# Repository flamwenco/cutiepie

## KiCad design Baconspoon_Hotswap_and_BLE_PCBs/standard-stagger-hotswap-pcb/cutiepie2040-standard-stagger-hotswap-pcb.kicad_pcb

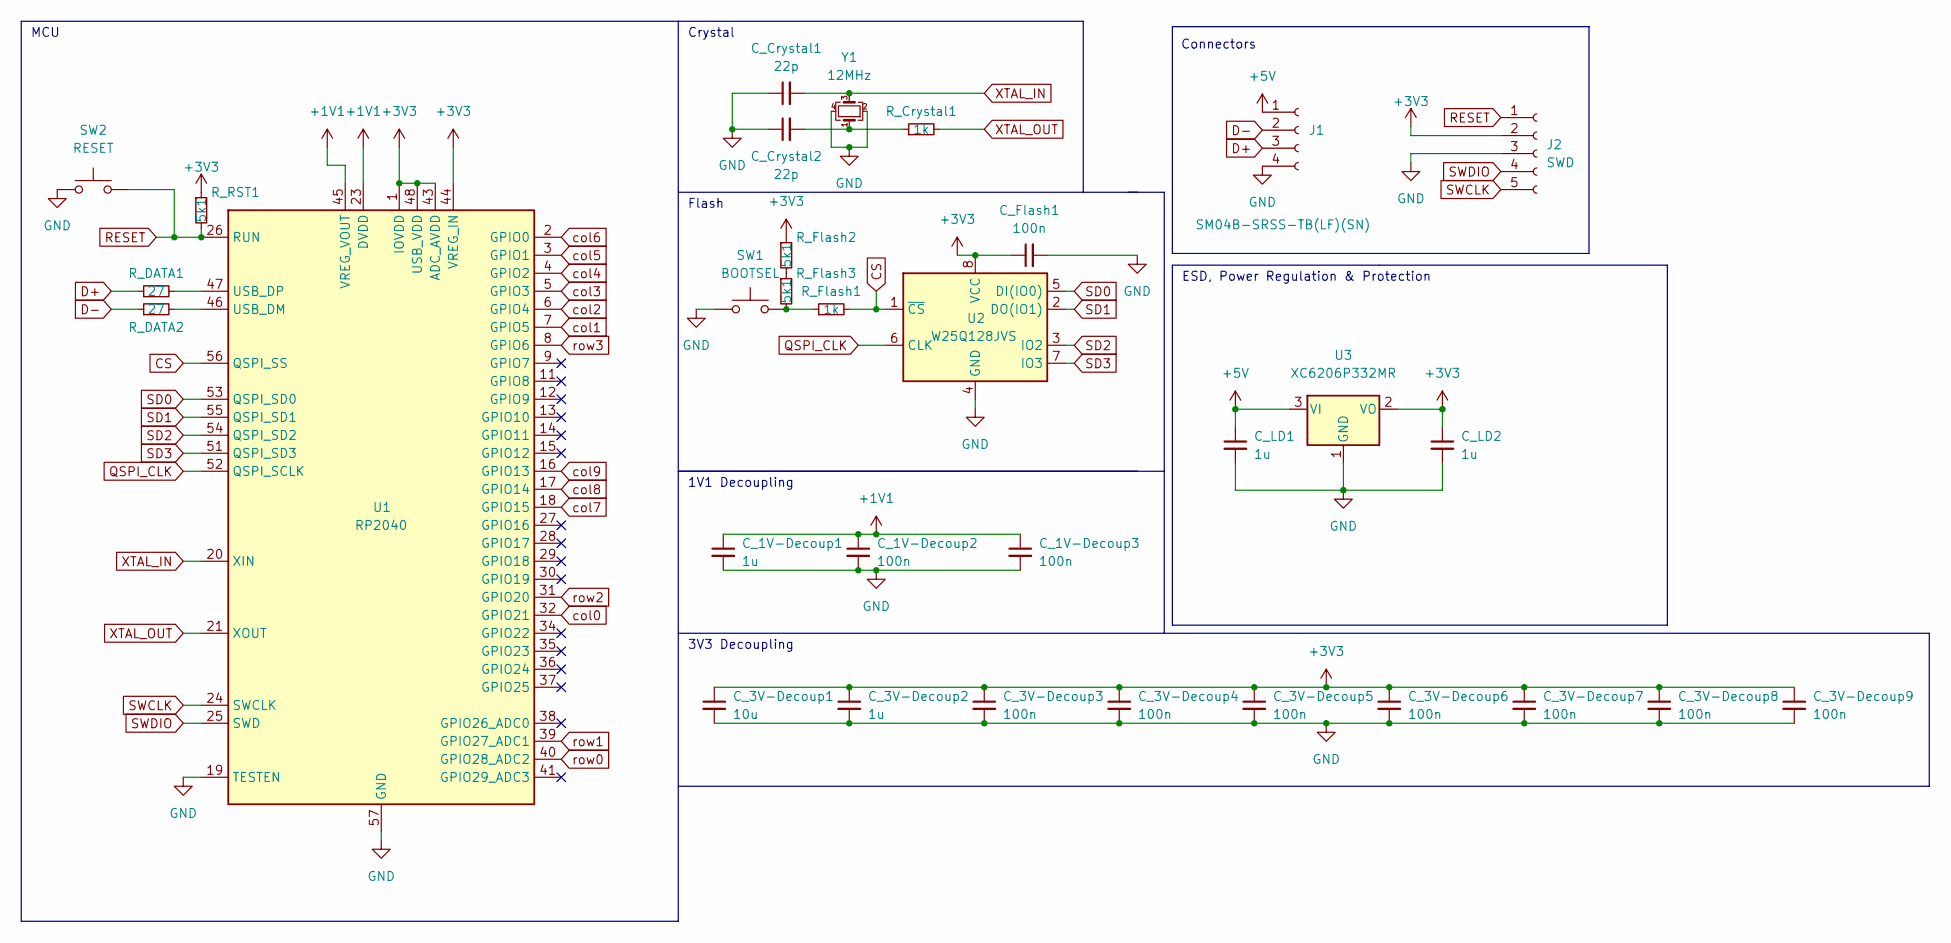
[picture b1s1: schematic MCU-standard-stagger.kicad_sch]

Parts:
C_1V-Decoup1, C_3V-Decoup2: 1u; C_0402_1005Metric
C_1V-Decoup2, C_1V-Decoup3, C_3V-Decoup3, C_3V-Decoup4, C_3V-Decoup5, C_3V-Decoup6, C_3V-Decoup7, C_3V-Decoup8, C_3V-Decoup9: 100n; C_0402_1005Metric
C_3V-Decoup1: 10u; C_0402_1005Metric
C_Crystal1, C_Crystal2: 22p; C_0402_1005Metric
C_Flash1: 100n; C_0402_1005Metric
C_LD1, C_LD2: 1u; C_0402_1005Metric
J1: SM04B-SRSS-TB(LF)(SN); JST_SH_SM04B-SRSS-TB_1x04-1MP_P1.00mm_Horizontal; LCSC C160404
J2: SWD; PinHeader_1x05_P2.54mm_Vertical
R_Crystal1: 1k; R_0402_1005Metric
R_DATA1, R_DATA2: 27; R_0402_1005Metric
R_Flash1: 1k; R_0402_1005Metric
R_Flash2, R_Flash3: 5k1; R_0402_1005Metric
R_RST1: 5k1; R_0402_1005Metric
SW1: BOOTSEL; SW_SPST_TL3342; LCSC C318884
SW2: RESET; SW_SPST_TL3342; LCSC C318884
U1: RP2040; RP2040-QFN-56; LCSC C2040
U2: W25Q128JVS; SOIC-8_5.23x5.23mm_P1.27mm; LCSC C2613930
U3: XC6206P332MR; SOT-23; LCSC C5446
Y1: 12MHz; Crystal_SMD_3225-4Pin_3.2x2.5mm; LCSC C9002

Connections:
+1V1: C_1V-Decoup1.1, C_1V-Decoup2.1, C_1V-Decoup3.1, U1.23 (DVDD), U1.45 (VREG_VOUT), U1.50 (DVDD)
+3V3: C_3V-Decoup1.1, C_3V-Decoup2.1, C_3V-Decoup3.1, C_3V-Decoup4.1, C_3V-Decoup5.1, C_3V-Decoup6.1, C_3V-Decoup7.1, C_3V-Decoup8.1, C_3V-Decoup9.1, C_Flash1.1, C_LD2.1, J2.2, R_Flash2.1, R_RST1.1, U1.1 (IOVDD), U1.10 (IOVDD), U1.22 (IOVDD), U1.33 (IOVDD), U1.42 (IOVDD), U1.43 (ADC_AVDD), U1.44 (VREG_IN), U1.48 (USB_VDD), U1.49 (IOVDD), U2.8 (VCC), U3.2 (VO)
+5V: C_LD1.1, J1.1, U3.3 (VI)
CS: R_Flash1.2, U1.56 (QSPI_SS), U2.1 (~CS)
D+: J1.3, R_DATA1.1
D-: J1.2, R_DATA2.1
GND: C_1V-Decoup1.2, C_1V-Decoup2.2, C_1V-Decoup3.2, C_3V-Decoup1.2, C_3V-Decoup2.2, C_3V-Decoup3.2, C_3V-Decoup4.2, C_3V-Decoup5.2, C_3V-Decoup6.2, C_3V-Decoup7.2, C_3V-Decoup8.2, C_3V-Decoup9.2, C_Crystal1.1, C_Crystal2.1, C_Flash1.2, C_LD1.2, C_LD2.2, J1.4, J2.3, SW1.1, SW2.1, U1.19 (TESTEN), U1.57 (GND), U2.4 (GND), U3.1 (GND), Y1.2, Y1.4
unnamed: C_Crystal2.2, R_Crystal1.1, Y1.1
unnamed: R_Flash1.1, R_Flash3.2, SW1.2
unnamed: R_Flash2.2, R_Flash3.1
unnamed: R_DATA2.2, U1.46 (USB_DM)
unnamed: R_DATA1.2, U1.47 (USB_DP)
QSPI_CLK: U1.52 (QSPI_SCLK), U2.6 (CLK)
RESET: J2.1, R_RST1.2, SW2.2, U1.26 (RUN)
SD0: U1.53 (QSPI_SD0), U2.5 (DI(IO0))
SD1: U1.55 (QSPI_SD1), U2.2 (DO(IO1))
SD2: U1.54 (QSPI_SD2), U2.3 (IO2)
SD3: U1.51 (QSPI_SD3), U2.7 (IO3)
SWCLK: J2.5, U1.24 (SWCLK)
SWDIO: J2.4, U1.25 (SWD)
XTAL_IN: C_Crystal1.2, U1.20 (XIN), Y1.3
XTAL_OUT: R_Crystal1.2, U1.21 (XOUT)
col0: U1.32 (GPIO21); also elsewhere on the board
col1: U1.7 (GPIO5); also elsewhere on the board
col2: U1.6 (GPIO4); also elsewhere on the board
col3: U1.5 (GPIO3); also elsewhere on the board
col4: U1.4 (GPIO2); also elsewhere on the board
col5: U1.3 (GPIO1); also elsewhere on the board
col6: U1.2 (GPIO0); also elsewhere on the board
col7: U1.18 (GPIO15); also elsewhere on the board
col8: U1.17 (GPIO14); also elsewhere on the board
col9: U1.16 (GPIO13); also elsewhere on the board
row0: U1.40 (GPIO28_ADC2); also elsewhere on the board
row1: U1.39 (GPIO27_ADC1); also elsewhere on the board
row2: U1.31 (GPIO20); also elsewhere on the board
row3: U1.8 (GPIO6); also elsewhere on the board

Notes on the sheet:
Connectors
1V1 Decoupling
ESD, Power Regulation & Protection
Crystal
MCU
Flash
3V3 Decoupling

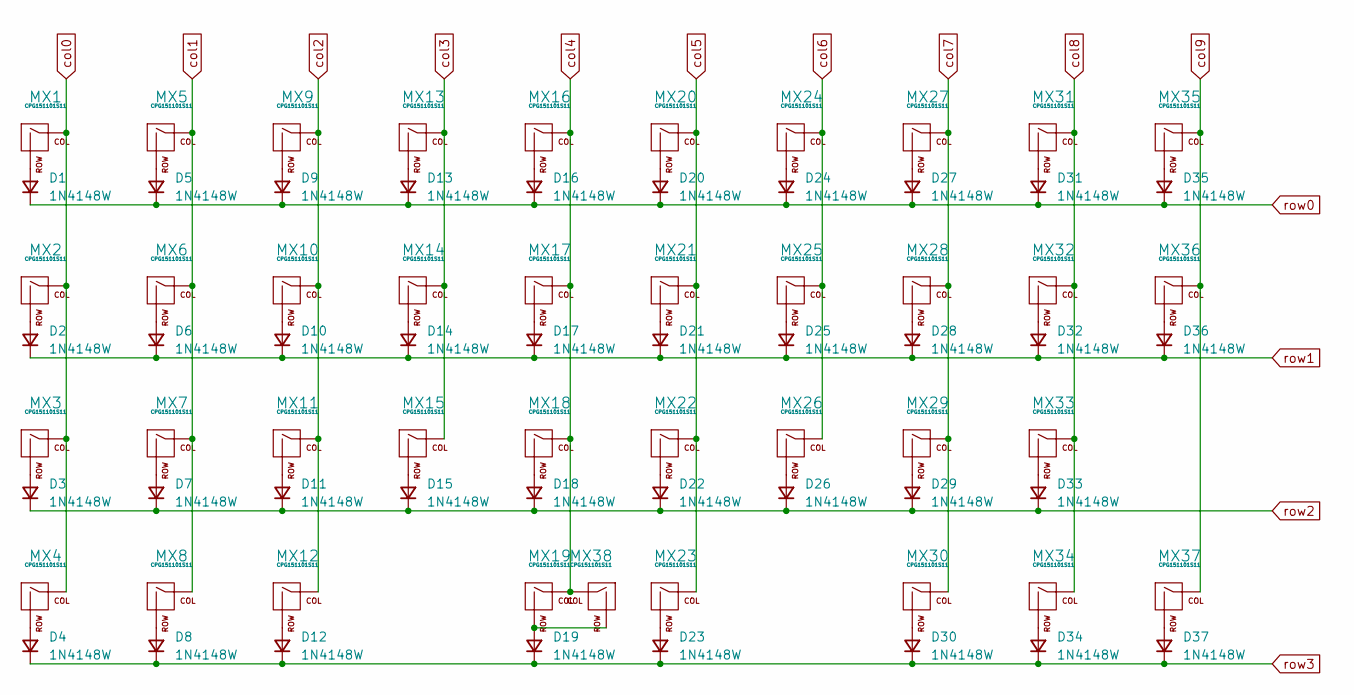
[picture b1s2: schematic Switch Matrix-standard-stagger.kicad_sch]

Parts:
D1, D2, D3, D4, D5, D6, D7, D8, D9, D10, D11, D12, D13, D14, D15, D16, D17, D18, D19, D20, D21, D22, D23, D24, D25, D26, D27, D28, D29, D30, D31, D32, D33, D34, D35, D36, D37: 1N4148W; D_SOD-123
MX1, MX4, MX5, MX6, MX7, MX8, MX9, MX10, MX11, MX12, MX13, MX14, MX15, MX16, MX17, MX18, MX20, MX21, MX22, MX24, MX25, MX26, MX27, MX28, MX29, MX30, MX31, MX32, MX34, MX37: CPG151101S11; MXOnly-1U-Hotswap; LCSC C2803348
MX2, MX36: CPG151101S11; MXOnly-1.25U-Hotswap; LCSC C2803348
MX3, MX33: CPG151101S11; MXOnly-1.75U-Hotswap; LCSC C2803348
MX19, MX23, MX38: CPG151101S11; MXOnly-2U-Hotswap-ReversedStabilizers; LCSC C2803348
MX35: CPG151101S11; MXOnly-1.5U-Hotswap; LCSC C2803348

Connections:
unnamed: D1.2 (A), MX1.2 (ROW)
unnamed: D2.2 (A), MX2.2 (ROW)
unnamed: D3.2 (A), MX3.2 (ROW)
unnamed: D4.2 (A), MX4.2 (ROW)
unnamed: D5.2 (A), MX5.2 (ROW)
unnamed: D6.2 (A), MX6.2 (ROW)
unnamed: D7.2 (A), MX7.2 (ROW)
unnamed: D8.2 (A), MX8.2 (ROW)
unnamed: D9.2 (A), MX9.2 (ROW)
unnamed: D10.2 (A), MX10.2 (ROW)
unnamed: D11.2 (A), MX11.2 (ROW)
unnamed: D12.2 (A), MX12.2 (ROW)
unnamed: D13.2 (A), MX13.2 (ROW)
unnamed: D14.2 (A), MX14.2 (ROW)
unnamed: D15.2 (A), MX15.2 (ROW)
unnamed: D16.2 (A), MX16.2 (ROW)
unnamed: D17.2 (A), MX17.2 (ROW)
unnamed: D18.2 (A), MX18.2 (ROW)
unnamed: D19.2 (A), MX19.2 (ROW), MX38.2 (ROW)
unnamed: D20.2 (A), MX20.2 (ROW)
unnamed: D21.2 (A), MX21.2 (ROW)
unnamed: D22.2 (A), MX22.2 (ROW)
unnamed: D23.2 (A), MX23.2 (ROW)
unnamed: D24.2 (A), MX24.2 (ROW)
unnamed: D25.2 (A), MX25.2 (ROW)
unnamed: D26.2 (A), MX26.2 (ROW)
unnamed: D27.2 (A), MX27.2 (ROW)
unnamed: D28.2 (A), MX28.2 (ROW)
unnamed: D29.2 (A), MX29.2 (ROW)
unnamed: D30.2 (A), MX30.2 (ROW)
unnamed: D31.2 (A), MX31.2 (ROW)
unnamed: D32.2 (A), MX32.2 (ROW)
unnamed: D33.2 (A), MX33.2 (ROW)
unnamed: D34.2 (A), MX34.2 (ROW)
unnamed: D35.2 (A), MX35.2 (ROW)
unnamed: D36.2 (A), MX36.2 (ROW)
unnamed: D37.2 (A), MX37.2 (ROW)
col0: MX1.1 (COL), MX2.1 (COL), MX3.1 (COL), MX4.1 (COL); also elsewhere on the board
col1: MX5.1 (COL), MX6.1 (COL), MX7.1 (COL), MX8.1 (COL); also elsewhere on the board
col2: MX9.1 (COL), MX10.1 (COL), MX11.1 (COL), MX12.1 (COL); also elsewhere on the board
col3: MX13.1 (COL), MX14.1 (COL), MX15.1 (COL); also elsewhere on the board
col4: MX16.1 (COL), MX17.1 (COL), MX18.1 (COL), MX19.1 (COL), MX38.1 (COL); also elsewhere on the board
col5: MX20.1 (COL), MX21.1 (COL), MX22.1 (COL), MX23.1 (COL); also elsewhere on the board
col6: MX24.1 (COL), MX25.1 (COL), MX26.1 (COL); also elsewhere on the board
col7: MX27.1 (COL), MX28.1 (COL), MX29.1 (COL), MX30.1 (COL); also elsewhere on the board
col8: MX31.1 (COL), MX32.1 (COL), MX33.1 (COL), MX34.1 (COL); also elsewhere on the board
col9: MX35.1 (COL), MX36.1 (COL), MX37.1 (COL); also elsewhere on the board
row0: D1.1 (K), D5.1 (K), D9.1 (K), D13.1 (K), D16.1 (K), D20.1 (K), D24.1 (K), D27.1 (K), D31.1 (K), D35.1 (K); also elsewhere on the board
row1: D2.1 (K), D6.1 (K), D10.1 (K), D14.1 (K), D17.1 (K), D21.1 (K), D25.1 (K), D28.1 (K), D32.1 (K), D36.1 (K); also elsewhere on the board
row2: D3.1 (K), D7.1 (K), D11.1 (K), D15.1 (K), D18.1 (K), D22.1 (K), D26.1 (K), D29.1 (K), D33.1 (K); also elsewhere on the board
row3: D4.1 (K), D8.1 (K), D12.1 (K), D19.1 (K), D23.1 (K), D30.1 (K), D34.1 (K), D37.1 (K); also elsewhere on the board

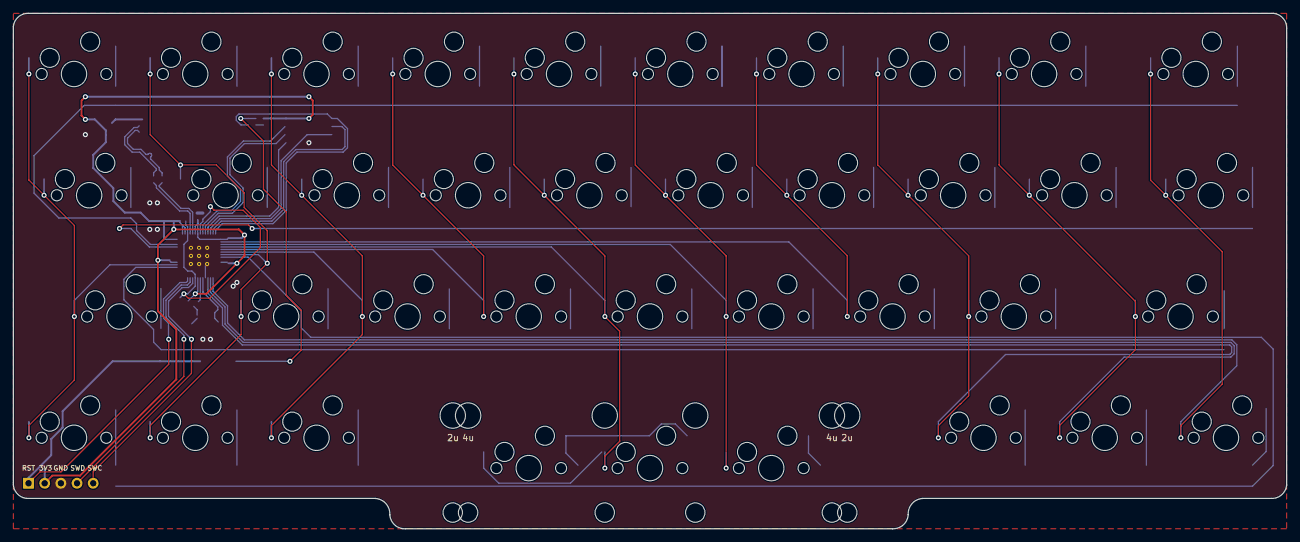
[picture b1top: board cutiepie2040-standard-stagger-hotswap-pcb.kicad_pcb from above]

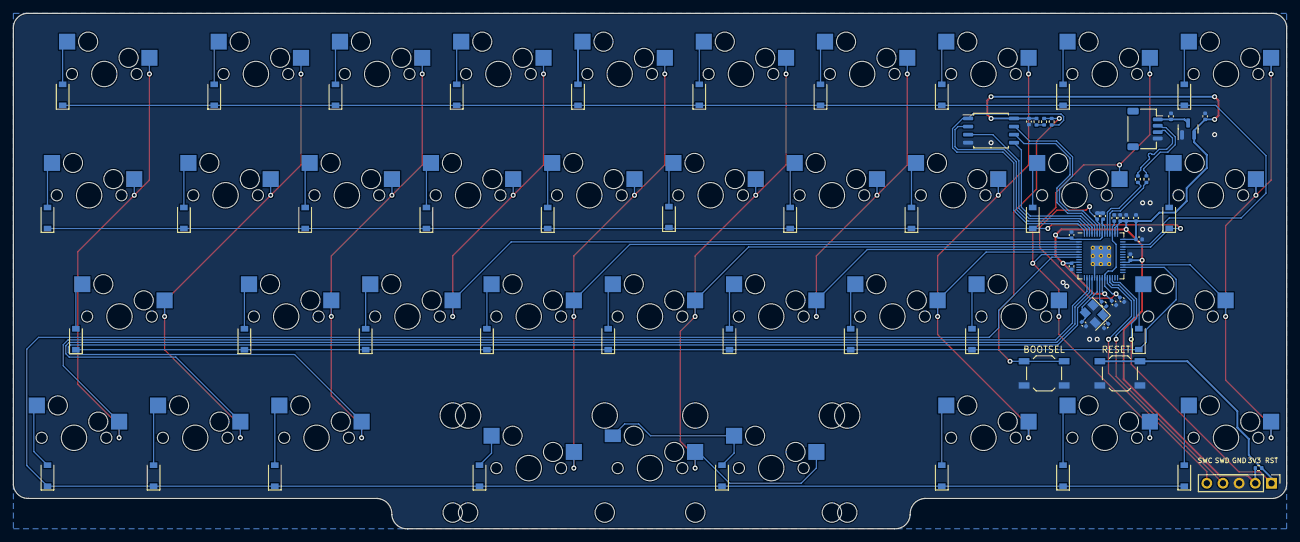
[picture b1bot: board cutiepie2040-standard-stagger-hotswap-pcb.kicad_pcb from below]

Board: 2 copper layers, 200.0 x 81.0 mm, 107 parts (107 on the bottom side), 73 nets.

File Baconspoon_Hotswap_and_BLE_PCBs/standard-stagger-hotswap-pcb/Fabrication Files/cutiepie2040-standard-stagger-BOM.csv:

Comment,Designator,Footprint,JLCPCB Part#(optional)
5K1,R_Flash2,R_0402_1005Metric,C103086
5K1,R_Flash3,R_0402_1005Metric,C103086
5K1,R_RST1,R_0402_1005Metric,C103086
10uF,C_3V-Decoup1,C_0402_1005Metric,C15525
22pF,C_Crystal1,C_0402_1005Metric,C1555
22pF,C_Crystal2,C_0402_1005Metric,C1555
SM04B-SRSS-TB(LF)(SN),J1,JST_SH_SM04B-SRSS-TB_1x04-1MP_P1.00mm_Horizontal,C160404
RP2040,U1,RP2040-QFN-56,C2040
27,R_DATA1,R_0402_1005Metric,C25100
27,R_DATA2,R_0402_1005Metric,C25100
W25Q128JVS,U2,SOIC-8_5.23x5.23mm_P1.27mm,C2613930
0.1uF,C_1V-Decoup2,C_0402_1005Metric,C2655418
0.1uF,C_1V-Decoup3,C_0402_1005Metric,C2655418
0.1uF,C_3V-Decoup3,C_0402_1005Metric,C2655418
0.1uF,C_3V-Decoup4,C_0402_1005Metric,C2655418
0.1uF,C_3V-Decoup5,C_0402_1005Metric,C2655418
0.1uF,C_3V-Decoup6,C_0402_1005Metric,C2655418
0.1uF,C_3V-Decoup7,C_0402_1005Metric,C2655418
0.1uF,C_3V-Decoup8,C_0402_1005Metric,C2655418
0.1uF,C_3V-Decoup9,C_0402_1005Metric,C2655418
0.1uF,C_Flash1,C_0402_1005Metric,C2655418
1K,R_Crystal1,R_0402_1005Metric,C279987
1K,R_Flash1,R_0402_1005Metric,C279987
CPG151101S11,MX1,MXOnly-1U-Hotswap,C2803348
CPG151101S11,MX10,MXOnly-1U-Hotswap,C2803348
CPG151101S11,MX11,MXOnly-1U-Hotswap,C2803348
CPG151101S11,MX12,MXOnly-1U-Hotswap,C2803348
CPG151101S11,MX13,MXOnly-1U-Hotswap,C2803348
CPG151101S11,MX14,MXOnly-1U-Hotswap,C2803348
CPG151101S11,MX15,MXOnly-1U-Hotswap,C2803348
CPG151101S11,MX16,MXOnly-1U-Hotswap,C2803348
CPG151101S11,MX17,MXOnly-1U-Hotswap,C2803348
CPG151101S11,MX18,MXOnly-1U-Hotswap,C2803348
CPG151101S11,MX19,MXOnly-2U-Hotswap-ReversedStabilizers,C2803348
CPG151101S11,MX2,MXOnly-1.25U-Hotswap,C2803348
CPG151101S11,MX20,MXOnly-1U-Hotswap,C2803348
CPG151101S11,MX21,MXOnly-1U-Hotswap,C2803348
CPG151101S11,MX22,MXOnly-1U-Hotswap,C2803348
CPG151101S11,MX23,MXOnly-2U-Hotswap-ReversedStabilizers,C2803348
CPG151101S11,MX24,MXOnly-1U-Hotswap,C2803348
CPG151101S11,MX25,MXOnly-1U-Hotswap,C2803348
CPG151101S11,MX26,MXOnly-1U-Hotswap,C2803348
CPG151101S11,MX27,MXOnly-1U-Hotswap,C2803348
CPG151101S11,MX28,MXOnly-1U-Hotswap,C2803348
CPG151101S11,MX29,MXOnly-1U-Hotswap,C2803348
CPG151101S11,MX3,MXOnly-1.5U-Hotswap,C2803348
CPG151101S11,MX30,MXOnly-1U-Hotswap,C2803348
CPG151101S11,MX31,MXOnly-1U-Hotswap,C2803348
CPG151101S11,MX32,MXOnly-1U-Hotswap,C2803348
CPG151101S11,MX33,MXOnly-1U-Hotswap,C2803348
CPG151101S11,MX34,MXOnly-1U-Hotswap,C2803348
CPG151101S11,MX35,MXOnly-1.5U-Hotswap,C2803348
CPG151101S11,MX36,MXOnly-1.25U-Hotswap,C2803348
CPG151101S11,MX37,MXOnly-1U-Hotswap,C2803348
CPG151101S11,MX38,MXOnly-1U-Hotswap,C2803348
CPG151101S11,MX4,MXOnly-1U-Hotswap,C2803348
CPG151101S11,MX5,MXOnly-1U-Hotswap,C2803348
CPG151101S11,MX6,MXOnly-1U-Hotswap,C2803348
CPG151101S11,MX7,MXOnly-1U-Hotswap,C2803348
CPG151101S11,MX8,MXOnly-1U-Hotswap,C2803348
CPG151101S11,MX9,MXOnly-1U-Hotswap,C2803348
BOOTSEL,SW1,SW_SPST_TL3342,C318884
RESET,SW2,SW_SPST_TL3342,C318884
1uF,C_1V-Decoup1,C_0402_1005Metric,C52923
1uF,C_3V-Decoup2,C_0402_1005Metric,C52923
1uF,C_LD1,C_0402_1005Metric,C52923
1uF,C_LD2,C_0402_1005Metric,C52923
XC6206P332MR,U3,SOT-23,C5446
1N4148W,D1,D_SOD-123,C81598
1N4148W,D10,D_SOD-123,C81598
1N4148W,D11,D_SOD-123,C81598
1N4148W,D12,D_SOD-123,C81598
1N4148W,D13,D_SOD-123,C81598
1N4148W,D14,D_SOD-123,C81598
1N4148W,D15,D_SOD-123,C81598
1N4148W,D16,D_SOD-123,C81598
1N4148W,D17,D_SOD-123,C81598
1N4148W,D18,D_SOD-123,C81598
1N4148W,D19,D_SOD-123,C81598
1N4148W,D2,D_SOD-123,C81598
1N4148W,D20,D_SOD-123,C81598
1N4148W,D21,D_SOD-123,C81598
1N4148W,D22,D_SOD-123,C81598
1N4148W,D23,D_SOD-123,C81598
1N4148W,D24,D_SOD-123,C81598
1N4148W,D25,D_SOD-123,C81598
1N4148W,D26,D_SOD-123,C81598
1N4148W,D27,D_SOD-123,C81598
1N4148W,D28,D_SOD-123,C81598
1N4148W,D29,D_SOD-123,C81598
1N4148W,D3,D_SOD-123,C81598
1N4148W,D30,D_SOD-123,C81598
1N4148W,D31,D_SOD-123,C81598
1N4148W,D32,D_SOD-123,C81598
1N4148W,D33,D_SOD-123,C81598
1N4148W,D34,D_SOD-123,C81598
1N4148W,D35,D_SOD-123,C81598
1N4148W,D36,D_SOD-123,C81598
1N4148W,D37,D_SOD-123,C81598
1N4148W,D4,D_SOD-123,C81598
1N4148W,D5,D_SOD-123,C81598
1N4148W,D6,D_SOD-123,C81598
1N4148W,D7,D_SOD-123,C81598
1N4148W,D8,D_SOD-123,C81598
1N4148W,D9,D_SOD-123,C81598
X322512MSB4SI,Y1,Crystal_SMD_3225-4Pin_3.2x2.5mm,C9002
